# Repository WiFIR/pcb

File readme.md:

# WiFI*R*

The WiFI*R* is a WiFi IR blaster / remote, based around a WeMos D1 mini (ESP8266)

The WiFIR was made from a need to control a heatpump / ac to allow pre-heating of a summer-house before arriving. It can however control anything IR controlled.

[Interactive BOM](https://WiFIR.github.io/pcb/ibom.html)

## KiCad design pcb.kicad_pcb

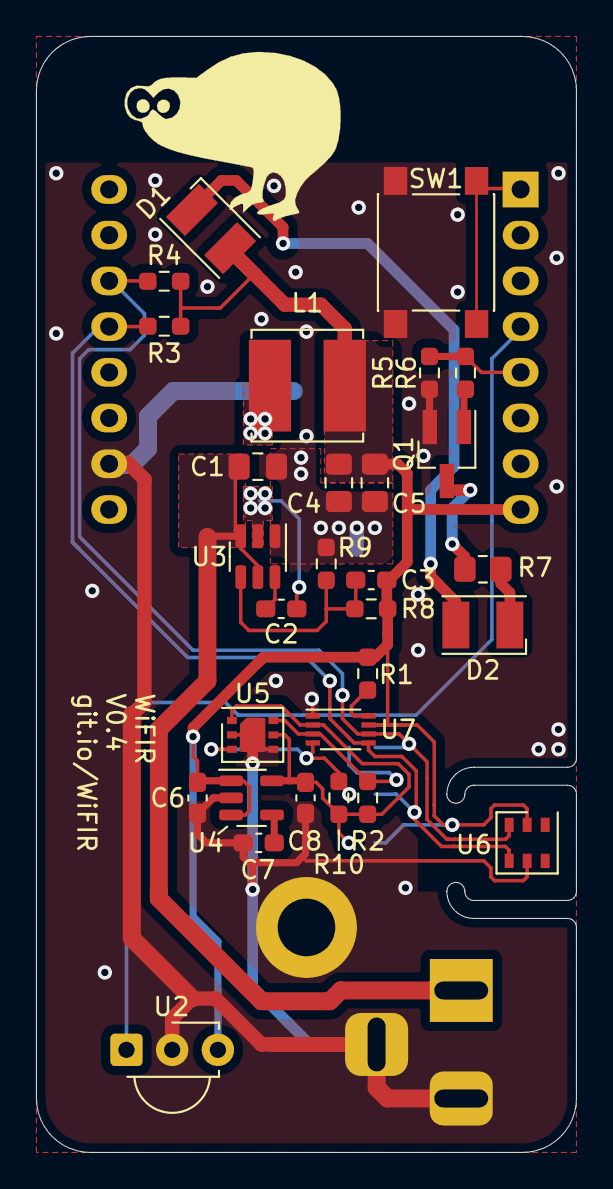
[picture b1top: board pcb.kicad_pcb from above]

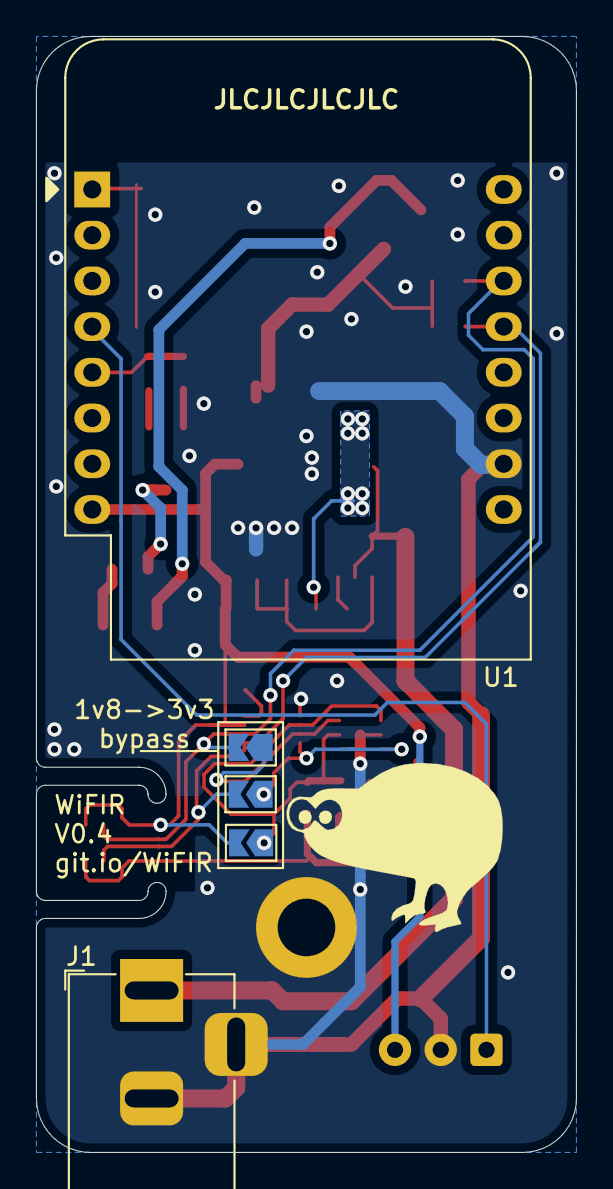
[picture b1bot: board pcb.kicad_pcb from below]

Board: 2 copper layers, 30.0 x 62.0 mm, 34 parts (5 on the bottom side), 20 nets.

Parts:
C1: 10uF; C_0805_2012Metric_Pad1.18x1.45mm_HandSolder
C2: 100nF; C_0603_1608Metric_Pad1.08x0.95mm_HandSolder
C3: 47pF; C_0603_1608Metric_Pad1.08x0.95mm_HandSolder
C4: 22uF: CL10A226MP8NUNE; C_0805_2012Metric_Pad1.18x1.45mm_HandSolder
C5: 22uF; C_0805_2012Metric_Pad1.18x1.45mm_HandSolder
C6, C8: 1uF; C_0603_1608Metric_Pad1.08x0.95mm_HandSolder
C7: 22nF; C_0603_1608Metric_Pad1.08x0.95mm_HandSolder
D1, D2: VSML3710-GS18; LED_PLCC-2
J1: 12V; BarrelJack_Horizontal
JP1: 1v8-bp; SolderJumper-2_P1.3mm_Open_TrianglePad1.0x1.5mm
JP2: sda-bp; SolderJumper-2_P1.3mm_Open_TrianglePad1.0x1.5mm
JP3: scl-bp; SolderJumper-2_P1.3mm_Open_TrianglePad1.0x1.5mm
L1: 100μH; L_Bourns_SRN6045TA
Q1: FDN339AN; SOT-23_Handsoldering
R1, R9: 22k; R_0603_1608Metric_Pad0.98x0.95mm_HandSolder
R2, R3, R4, R5, R10: 4k7; R_0603_1608Metric_Pad0.98x0.95mm_HandSolder
R6: 470R; R_0603_1608Metric_Pad0.98x0.95mm_HandSolder
R7: 1R5; R_0805_2012Metric_Pad1.20x1.40mm_HandSolder
R8: 100k; R_0603_1608Metric_Pad0.98x0.95mm_HandSolder
SW1: SW_SPST; SW_Push_1P1T_NO_6x6mm_H9.5mm
U1: WeMos_D1_mini; WEMOS_D1_mini_light
U2: TSOP38236; Vishay_MINICAST-3Pin
U3: TPS54302; SOT-23-6
U4: AP131-18; SOT-23-5
U5: SGP30; Sensirion_DFN-6-1EP_2.45x2.45mm_P0.8mm_EP1.25x1.7mm
U6: AHT20; Asair_LGA-6_3x3mm_P1mm
U7: PCA9306DC1; VSSOP-8_2.3x2mm_P0.5mm

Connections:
+1V8: C8.2, JP1.1 (A), R2.2, R10.2, U4.5 (OUT), U5.1 (VDD), U5.5 (VDDH), U7.2 (VREF1)
+3V3: C3.2, C4.2, C5.2, C6.2, D1.2 (A), JP1.2 (B), L1.2, R1.2, R3.2, R4.2, R8.2, U1.8 (3V3), U2.3 (Vs), U4.1 (IN), U4.3 (EN), U6.2 (VDD), U7.7 (VREF2)
/SCL_1V8: JP2.1 (A), R2.1, U5.6 (SCL), U7.3 (SCL1)
/SCL_3V3: JP2.2 (B), R4.1, U1.14 (SCL/D1), U6.3 (SCL), U7.6 (SCL2)
/SDA_1V8: JP3.1 (A), R10.1, U5.3 (SDA), U7.4 (SDA1)
/SDA_3V3: JP3.2 (B), R3.1, U1.13 (SDA/D2), U6.4 (SDA), U7.5 (SDA2)
GND: C1.2, C4.1, C5.1, C6.1, C7.1, C8.1, J1.2, J1.3, Q1.2 (S), R5.1, R9.1, SW1.1 (A), U1.10 (GND), U2.2 (GND), U3.1 (GND), U4.2 (GND), U5.2 (VSS), U5.4 (R), U5.7 (pad), U6.5 (GND), U7.1 (GND)
IR_BLAST: R5.2, R6.1, U1.5 (MISO/D6)
IR_SIGNAL: U1.4 (SCK/D5), U2.1 (OUT)
unnamed: C2.1, L1.1, U3.2 (SW)
unnamed: C2.2, U3.6 (BOOT)
unnamed: C3.1, R8.1, R9.2, U3.4 (FB)
unnamed: C7.2, U4.4 (BP)
unnamed: D1.1 (K), D2.2 (A)
unnamed: D2.1 (K), R7.1
unnamed: Q1.1 (G), R6.2
unnamed: Q1.3 (D), R7.2
unnamed: R1.1, U7.8 (EN)
unnamed: SW1.2 (B), U1.1 (~RST)
VCC: C1.1, J1.1, U3.3 (VIN), U3.5 (EN)

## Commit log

2020-09-02 Tested working hardware.
2020-09-02 Fixed ibom link
2020-09-04 Implemented on-board cell protection to allow the use of un-protected cells
2020-09-04 Updated s pdf schematic
2020-09-04 Updated schematic info
2020-09-04 Actually push schematic
2020-09-07 Did stuff
2020-09-10 Redesigned to small-stick formfactor
2020-09-10 Added alternative fuel gauge to PCB
2020-09-23 Added stuff
2020-09-23 Updated schematic
2021-02-03 Made it nicer
2021-03-18 v0.4 production
2021-03-31 Use 220uH inductor and emitter follower LED driver
